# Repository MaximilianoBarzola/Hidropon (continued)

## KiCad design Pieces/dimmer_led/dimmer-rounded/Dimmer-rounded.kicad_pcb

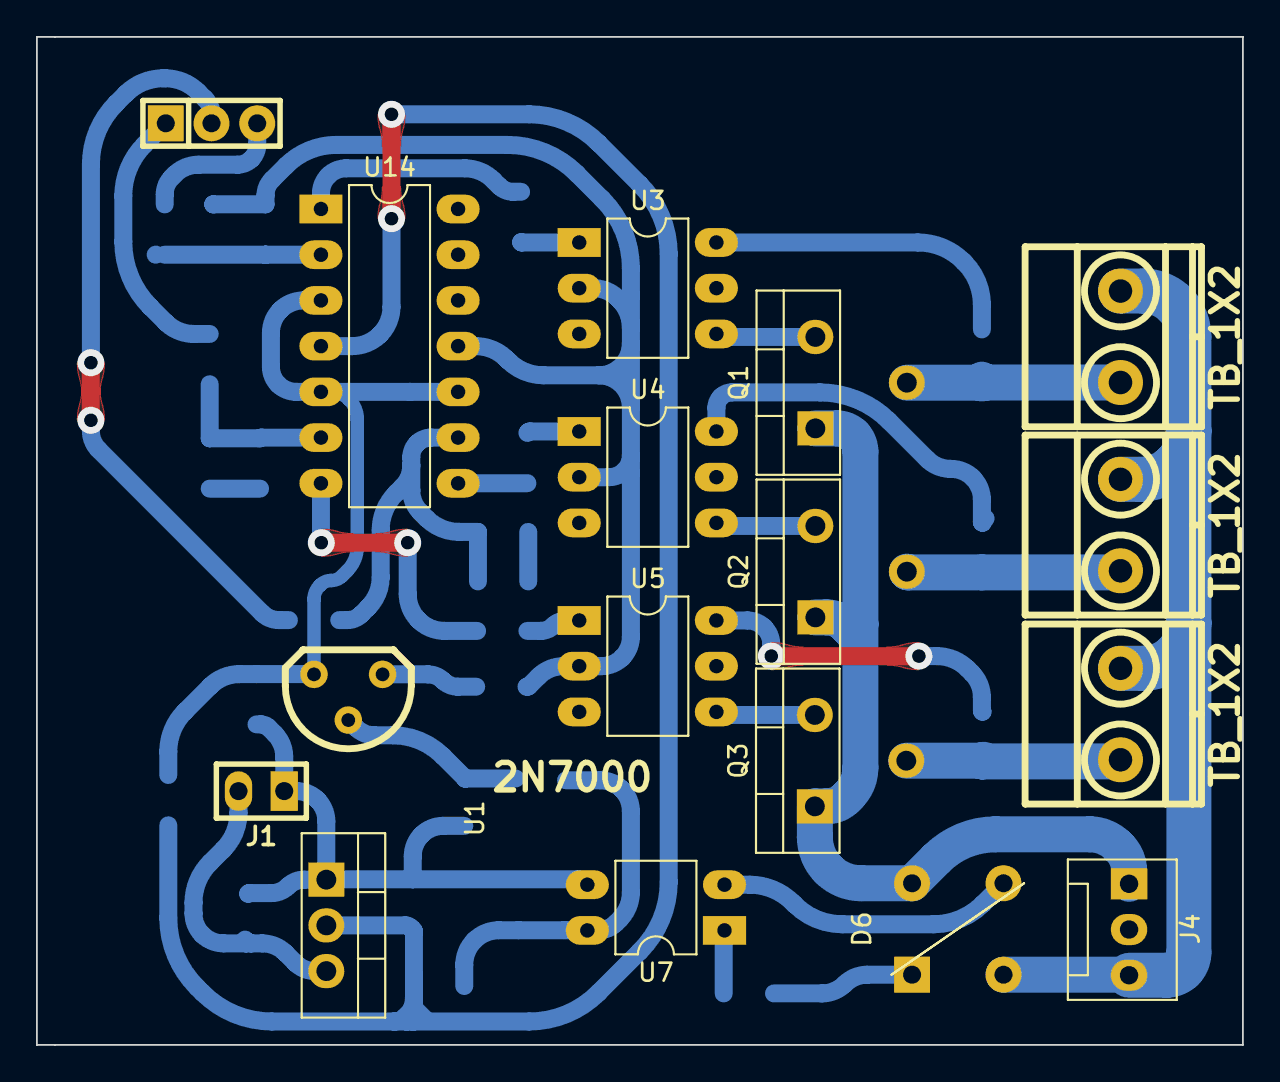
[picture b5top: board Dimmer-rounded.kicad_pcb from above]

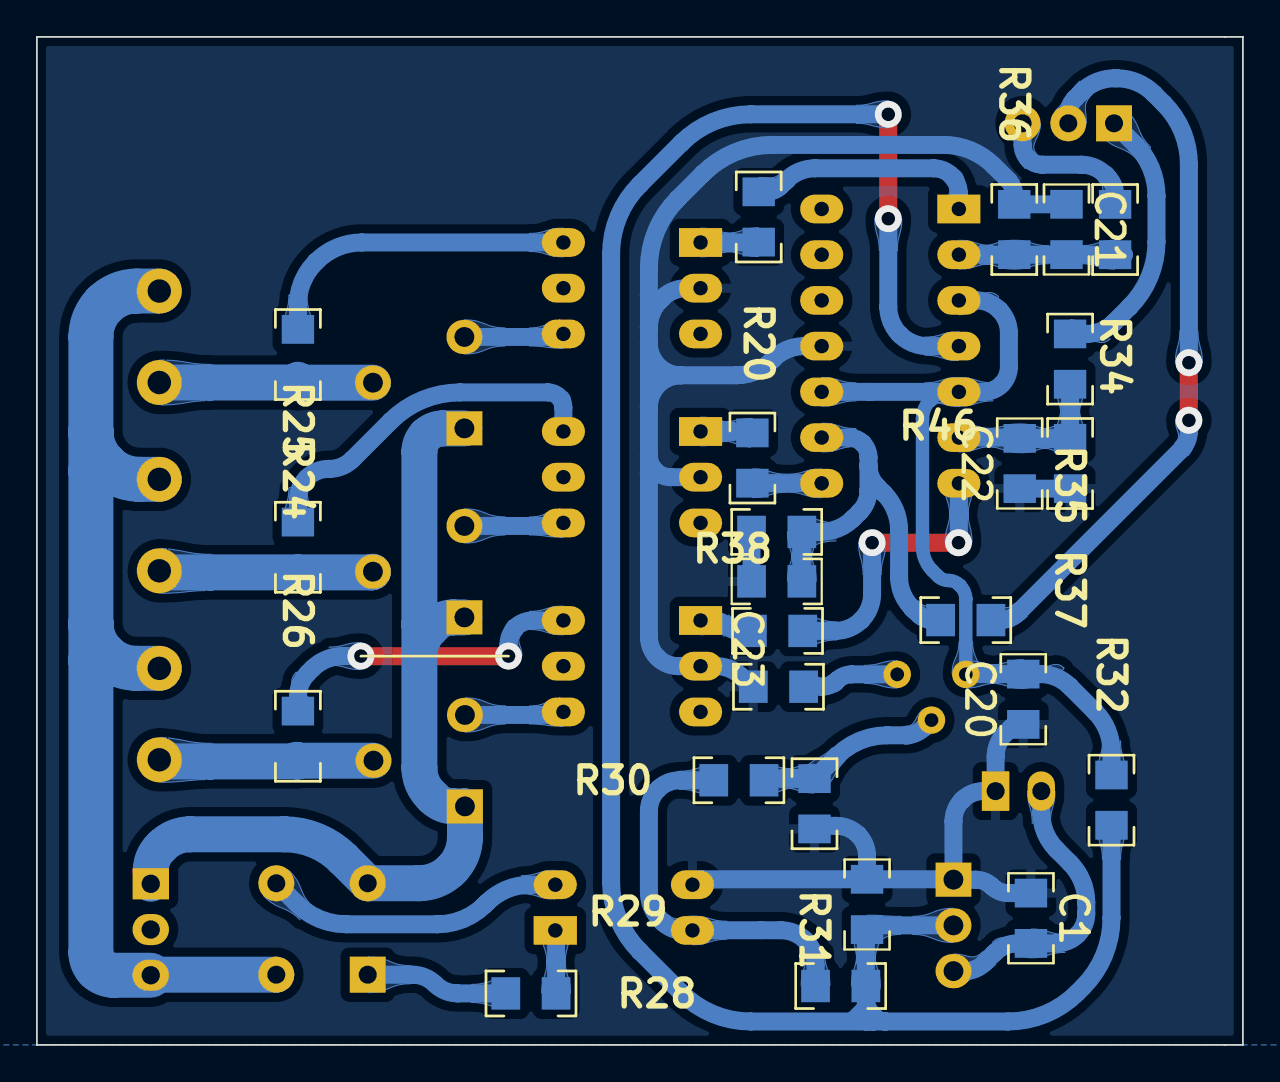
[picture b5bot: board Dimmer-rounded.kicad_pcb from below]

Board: 2 copper layers, 67.0 x 56.0 mm, 41 parts (24 on the bottom side), 33 nets.

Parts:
C1: 220nf; C_1206
C2, C20: 100nf; C_1206
C21, C22, C23: 1uf; C_1206
D6: D_Bridge_+A-A; Diode_Bridge_Round_D8.9mm
J1: Conn_01x02_Female; Pin_strip_2
J2: Conn_01X03; Pin_Strip_3
J3, J5, J6: TB_1X2; BORNERA2
J4: Conn_01x03_Female; FanPinHeader_1x03_P2.54mm_Vertical
Q1, Q2, Q3: BTA06-600C; TO-220-3_Vertical_ac
Q5: 2N7000; to92
R20, R21, R22: 220; R_1206
R24, R25, R26: 180; R_1206
R28: 33k; R_1206
R29, R30, R33: 1k; R_1206
R31, R34, R35, R38: 10k; R_1206
R32: 100k; R_1206
R36, R37, R46: 470k; R_1206
U1: LM78XX; TO-220-3_Vertical
U3, U4, U5: MOC3020M; DIP-6
U7: PC817; DIP-4
U14: LM324; DIP-14

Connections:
+5V: C2.1, R29.1, R32.1, U1.2 (VOUT), U14.4 (V+)
+12V: C1.1, J1.2, U1.3 (VIN)
/Int1: J2.3, R34.1
/Int2: J2.2, R38.1
/Int3: J2.1, R35.1
/OUT: C20.1, Q5.3 (D), R32.2, U14.3 (+), U14.5 (+), U14.10 (+)
/OUT_1: R20.1, U14.1
/OUT_2: R21.2, U14.8
/OUT_3: R22.2, U14.7
AC: D6.4, J4.1, Q1.1 (A1), Q2.1 (A1), Q3.1 (A1)
Earth: D6.2, J3.2, J4.3, J5.2, J6.2
GND: C1.2, C2.2, C20.2, C21.2, C22.2, C23.2, J1.1, R31.2, R33.2, R36.2, R37.2, R46.2, U1.1 (ADJ/GND), U3.2, U4.2, U5.2, U7.3, U14.11 (V-)
unnamed: C21.1, R34.2, R36.1, U14.2 (-)
unnamed: C22.1, R35.2, R37.1, U14.6 (-)
unnamed: C23.1, R38.2, R46.1, U14.9 (-)
unnamed: D6.1 (+), R28.1
unnamed: D6.3 (-), U7.2
unnamed: J3.1, Q1.2 (A2), R24.2
unnamed: J5.1, Q2.2 (A2), R25.1
unnamed: J6.1, Q3.2 (A2), R26.1
unnamed: Q1.3 (G), U3.4
unnamed: Q2.3 (G), U4.4
unnamed: Q3.3 (G), U5.4
unnamed: Q5.1 (S), R33.1
unnamed: Q5.2 (G), R30.1, R31.1
unnamed: R20.2, U3.1
unnamed: R21.1, U4.1
unnamed: R22.1, U5.1
unnamed: R24.1, U3.6
unnamed: R25.2, U4.6
unnamed: R26.2, U5.6
unnamed: R28.2, U7.1
unnamed: R29.2, R30.2, U7.4

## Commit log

2022-06-01 Start
2022-06-02 New Tasks
2022-06-08 Obisidan management system
2022-06-09 Medidor_TDS
2022-06-09 Tasks updated
2022-06-18 nose
2022-06-18 terminado dimmer
2022-06-19 pcb actualizado
2022-06-20 lista de componentes
2022-06-22 dimmer actualizado
2022-06-23 medido tds y ph
2022-06-23 pcbs
2022-06-24 le agregue las medidas jajajajajajajxd
2022-08-04 Actualizada los tasks
2022-08-28 housing desing
